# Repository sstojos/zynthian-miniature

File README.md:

# zynthian-miniature
# Overview
This is repository that store schematics and PCB design for basic PCB with MIDIs, Sound Card and 4 encoders for [zynthian](https://www.zynthian.org). It can also be used for any other raspberry pi audio software. 

This is designed in KiCad 6.0. It is inspired by clumsy MIDI project.

It comes as a single PCB that need to be split into 5: one main PCB and 4 encoder PCBs.

Here is the KiCad schematics screenshot:

# BOM
Interactive BOM can be found [here](https://raw.githack.com/sstojos/zynthian-miniature/main/bom/ibom.html).

# Usage scenarious

## JST connectors can be replaced with pinheader connectors
Connectors for encoder wiring are JST 2.5mm connectors but standard 2.54mm pin header connectors can also be used instead.

## PCB mounted MIDI connectors can be replaced with panel mounted MIDI connectors
It can be also used  with MIDI and AUDIO panel connectors. Here is how would you wire external panel connectors.

NOTE: Due to limited size of raspberry pi HUT, JST connectors for MIDI panel connectors are in the same place on PCB where two (IN and OUT) MIDI PCB mountable connectors are. Therefore you can only install JST connectors or MIDI PCB connectors but not both on the same PCB. MIDI through connector is only available through JST connector.

## It can be used with another sound card 
Sound card must not be installed if another sound card is connected to raspberry pi. I2S sound cards can not share the same rpi pins.

NOTE: can not be used with another audio card that have AUDIO IN (ADC) such as Hifyberry DAC+ ADC or DAC2 PRO ADC because encoder 3 B pin is wired to RPI pin 38 which is often  used by audio cards with ADC for audio in data. In this case there is a need to brake line from encoder 3 B connector to rpi 38 pin on PCB and  patch (solder wire) from encoder 3 b pin to another available rpi pin. Finnaly, wiring configuration in zynthian webconfig need to be changed accordingly. It is an easy patch. 

# Zynthian Webconfig

## Sound Card
Audio: HifiBerry DAC+ light

## Wiring
* Wiring Layout: Dummies
* Advance Configuration: Enabled
* Encoders A-pins: 5,3,28,23
* Encoders B-pins: 4,2,27,22
* Switches pins: 7,25,26,21

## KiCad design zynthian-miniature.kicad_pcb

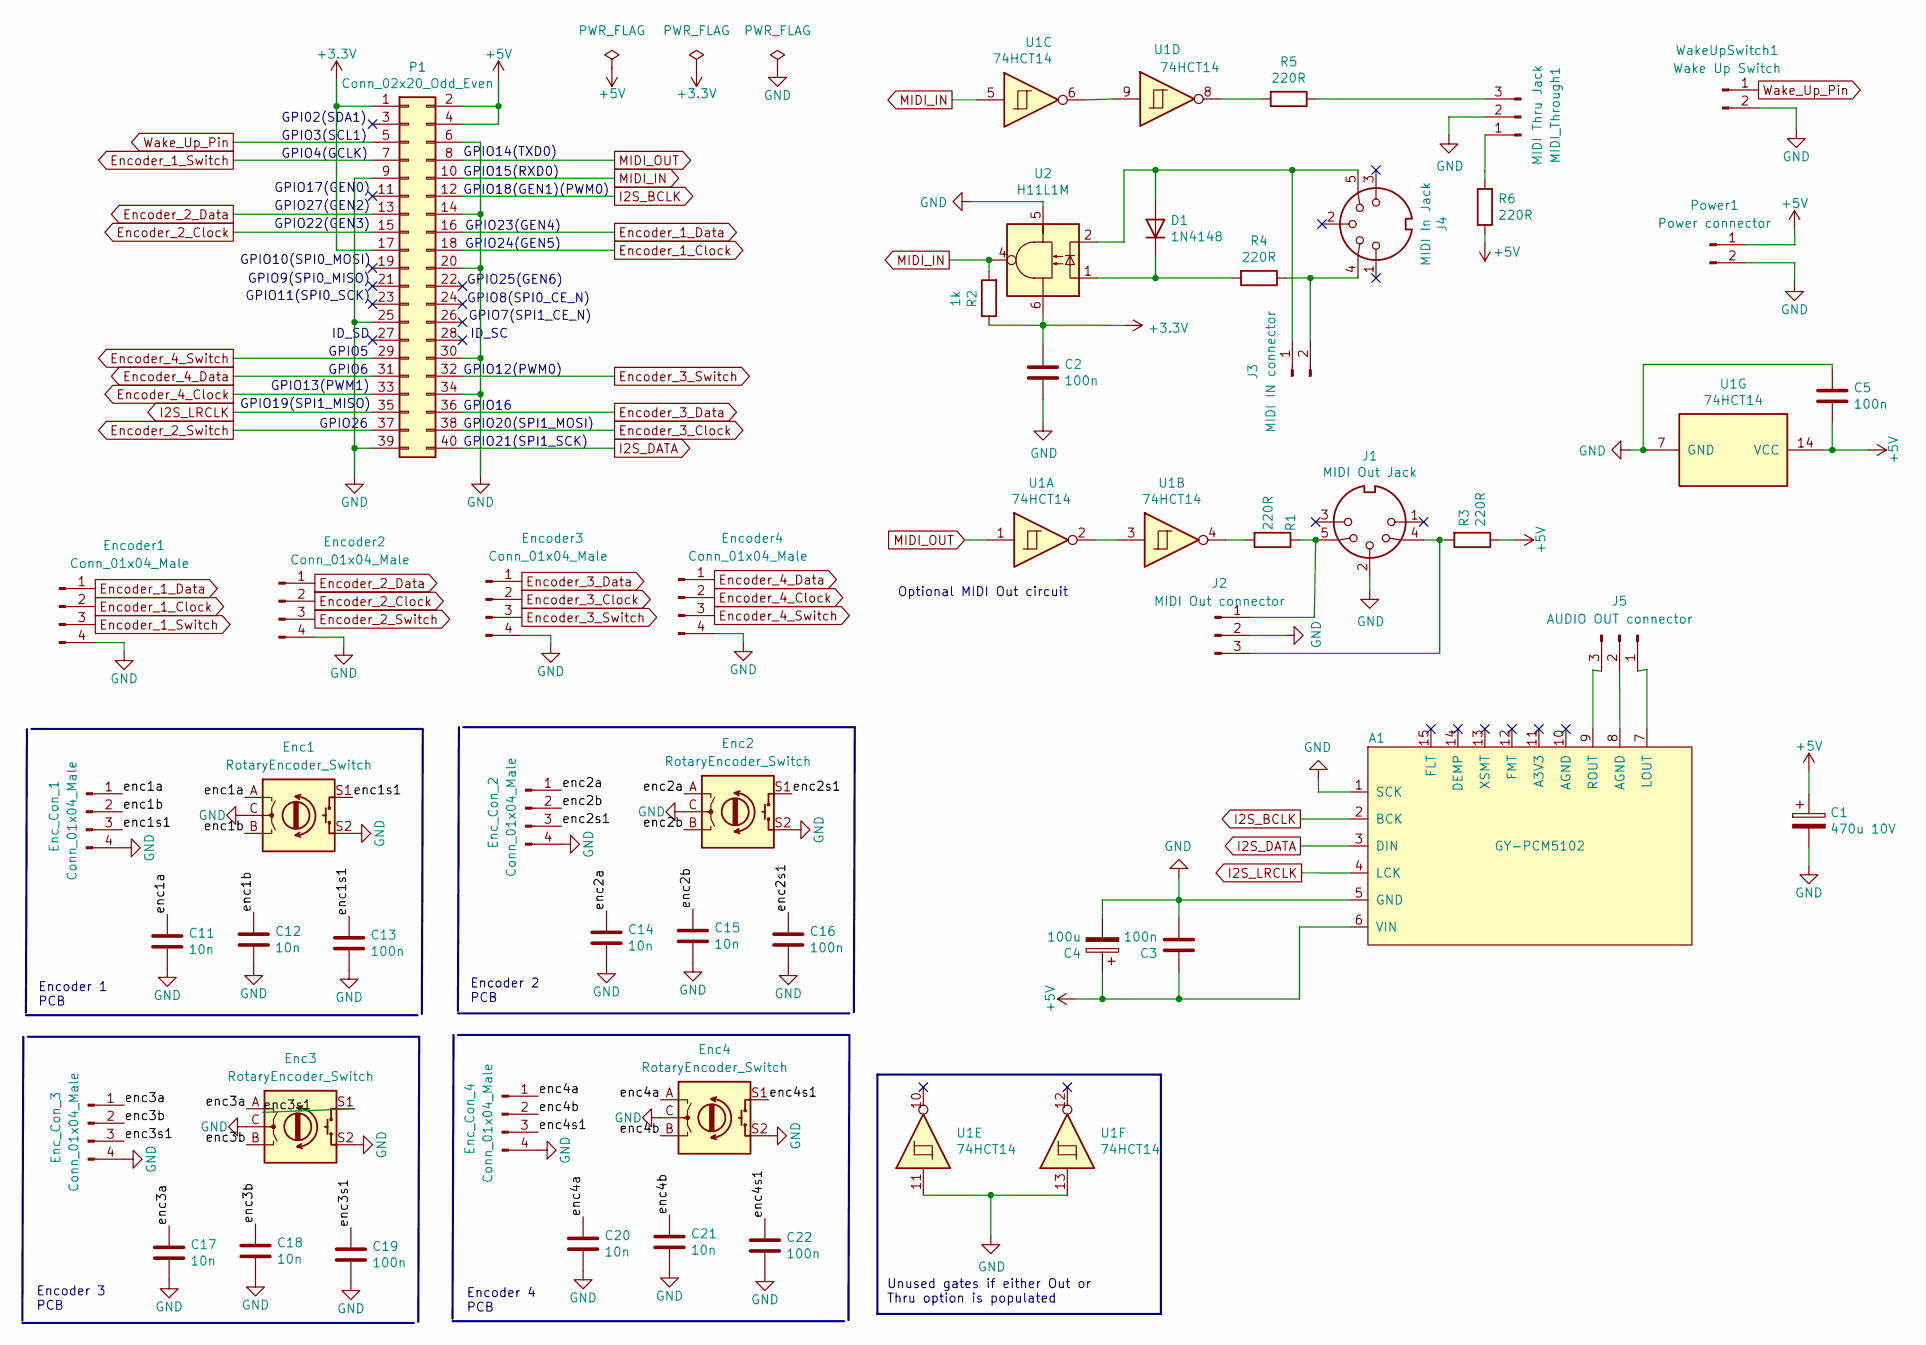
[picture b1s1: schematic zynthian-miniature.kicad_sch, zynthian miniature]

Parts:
A1: GY-PCM5102
C1: 470u 10V; CP_Radial_D8.0mm_P3.50mm
C2, C3, C5: 100n; C_Rect_L7.0mm_W2.0mm_P5.00mm
C4: 100u; CP_Radial_D6.3mm_P2.50mm
C11, C12, C14, C15, C17, C18, C20, C21: 10n; C_Rect_L4.0mm_W2.5mm_P2.50mm
C13, C16, C19, C22: 100n; C_Rect_L4.0mm_W2.5mm_P2.50mm
D1: 1N4148; D_DO-35_SOD27_P7.62mm_Horizontal
Enc1, Enc2, Enc3, Enc4: RotaryEncoder_Switch; RotaryEncoder_Alps_EC12E-Switch_Vertical_H20mm
Enc_Con_1, Enc_Con_2, Enc_Con_3, Enc_Con_4: Conn_01x04_Male; PinHeader_1x04_P2.54mm_Vertical
Encoder1, Encoder2, Encoder3, Encoder4: Conn_01x04_Male; PinHeader_1x04_P2.54mm_Vertical
J1: MIDI Out Jack; MultiDIN5
J2: MIDI Out connector; PinHeader_1x03_P2.54mm_Vertical
J3: MIDI IN connector; PinHeader_1x02_P2.54mm_Vertical
J4: MIDI In Jack; MultiDIN5
J5: AUDIO OUT connector; PinHeader_1x03_P2.54mm_Vertical
MIDI_Through1: MIDI Thru Jack; PinHeader_1x03_P2.54mm_Vertical
P1: Conn_02x20_Odd_Even; PinSocket_2x20_P2.54mm_Vertical
Power1: Power connector; PinHeader_1x02_P2.54mm_Vertical
R1, R3, R4, R5, R6: 220R; R_Axial_DIN0207_L6.3mm_D2.5mm_P7.62mm_Horizontal
R2: 1k; R_Axial_DIN0207_L6.3mm_D2.5mm_P7.62mm_Horizontal
U1: 74HCT14; DIP-14_W7.62mm
U2: H11L1M; DIP-6_W7.62mm
WakeUpSwitch1: Wake Up Switch; PinHeader_1x02_P2.54mm_Vertical

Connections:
+3.3V: C2.1, P1.1, P1.17, R2.1, U2.6
+5V: A1.6 (VIN), C1.1, C3.1, C4.1, C5.2, P1.2, P1.4, Power1.1, R3.1, R6.1, U1.14 (VCC)
/enc1a: C11.1, Enc1.A, Enc_Con_1.1
/enc1b: C12.1, Enc1.B, Enc_Con_1.2
/enc1s1: C13.1, Enc1.S1, Enc_Con_1.3
/enc2a: C14.1, Enc2.A, Enc_Con_2.1
/enc2b: C15.1, Enc2.B, Enc_Con_2.2
/enc2s1: C16.1, Enc2.S1, Enc_Con_2.3
/enc3a: C17.1, Enc3.A, Enc_Con_3.1
/enc3b: C18.1, Enc3.B, Enc_Con_3.2
/enc3s1: C19.1, Enc3.S1, Enc_Con_3.3
/enc4a: C20.1, Enc4.A, Enc_Con_4.1
/enc4b: C21.1, Enc4.B, Enc_Con_4.2
/enc4s1: C22.1, Enc4.S1, Enc_Con_4.3
Encoder_1_Clock: Encoder1.2, P1.18
Encoder_1_Data: Encoder1.1, P1.16
Encoder_1_Switch: Encoder1.3, P1.7
Encoder_2_Clock: Encoder2.2, P1.15
Encoder_2_Data: Encoder2.1, P1.13
Encoder_2_Switch: Encoder2.3, P1.37
Encoder_3_Clock: Encoder3.2, P1.38
Encoder_3_Data: Encoder3.1, P1.36
Encoder_3_Switch: Encoder3.3, P1.32
Encoder_4_Clock: Encoder4.2, P1.33
Encoder_4_Data: Encoder4.1, P1.31
Encoder_4_Switch: Encoder4.3, P1.29
GND: A1.1 (SCK), A1.5 (GND), C1.2, C2.2, C3.2, C4.2, C5.1, C11.2, C12.2, C13.2, C14.2, C15.2, C16.2, C17.2, C18.2, C19.2, C20.2, C21.2, C22.2, Enc1.C, Enc1.S2, Enc2.C, Enc2.S2, Enc3.C, Enc3.S2, Enc4.C, Enc4.S2, Enc_Con_1.4, Enc_Con_2.4, Enc_Con_3.4, Enc_Con_4.4, Encoder1.4, Encoder2.4, Encoder3.4, Encoder4.4, J1.2, J2.2, MIDI_Through1.2, P1.6, P1.9, P1.14, P1.20, P1.25, P1.30, P1.34, P1.39, Power1.2, U1.7 (GND), U1.11, U1.13, U2.5, WakeUpSwitch1.2
I2S_BCLK: A1.2 (BCK), P1.12
I2S_DATA: A1.3 (DIN), P1.40
I2S_LRCLK: A1.4 (LCK), P1.35
MIDI_IN: P1.10, R2.2, U1.5, U2.4
MIDI_OUT: P1.8, U1.1
unnamed: A1.7 (LOUT), J5.1
unnamed: A1.8 (AGND), J5.2
unnamed: A1.9 (ROUT), J5.3
unnamed: D1.1 (K), R4.2, U2.1
unnamed: D1.2 (A), J3.1, J4.5, U2.2
unnamed: J1.4, J2.3, R3.2
unnamed: J1.5, J2.1, R1.1
unnamed: J3.2, J4.4, R4.1
unnamed: MIDI_Through1.1, R6.2
unnamed: MIDI_Through1.3, R5.1
unnamed: R1.2, U1.4
unnamed: R5.2, U1.8
unnamed: U1.2, U1.3
unnamed: U1.6, U1.9
Wake_Up_Pin: P1.5, WakeUpSwitch1.1

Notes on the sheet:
Encoder 1 PCB
GPIO13(PWM1)
ID_SC
GPIO22(GEN3)
GPIO7(SPI1_CE_N)
Encoder 3 PCB
GPIO12(PWM0)
Encoder 2 PCB
GPIO25(GEN6)
ID_SD
GPIO23(GEN4)
GPIO6
GPIO15(RXD0)
GPIO26
Encoder 4 PCB
GPIO10(SPI0_MOSI)
GPIO9(SPI0_MISO)
GPIO27(GEN2)
GPIO14(TXD0)
GPIO24(GEN5)
GPIO11(SPI0_SCK)
Optional MIDI Out circuit
GPIO5
GPIO19(SPI1_MISO)
Unused gates if either Out or Thru option is populated
GPIO17(GEN0)
GPIO4(GCLK)
GPIO8(SPI0_CE_N)
GPIO20(SPI1_MOSI)
GPI02(SDA1)
GPIO18(GEN1)(PWM0)
GPIO21(SPI1_SCK)
GPIO3(SCL1)
GPIO16

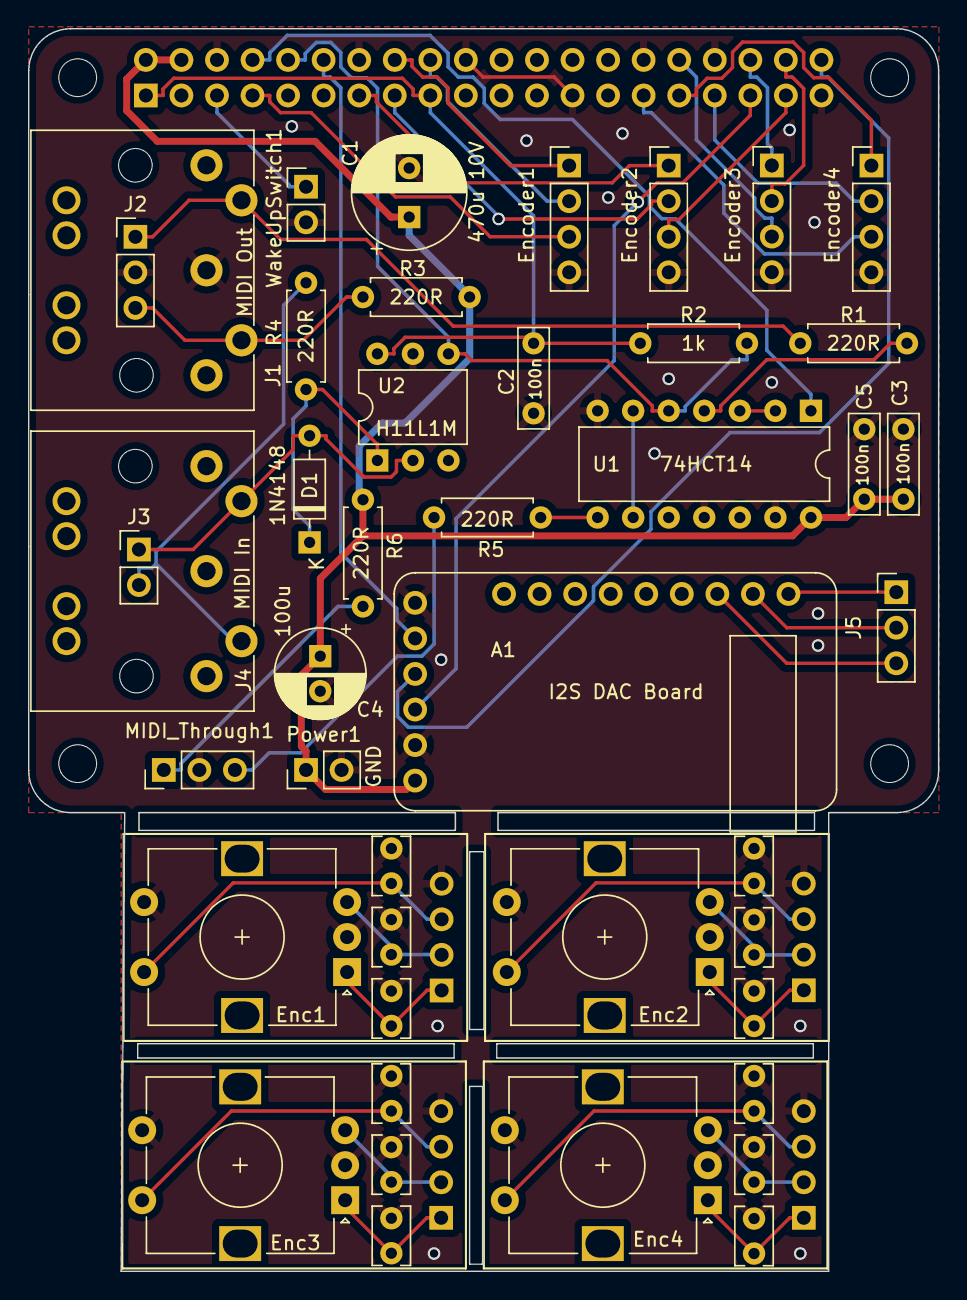
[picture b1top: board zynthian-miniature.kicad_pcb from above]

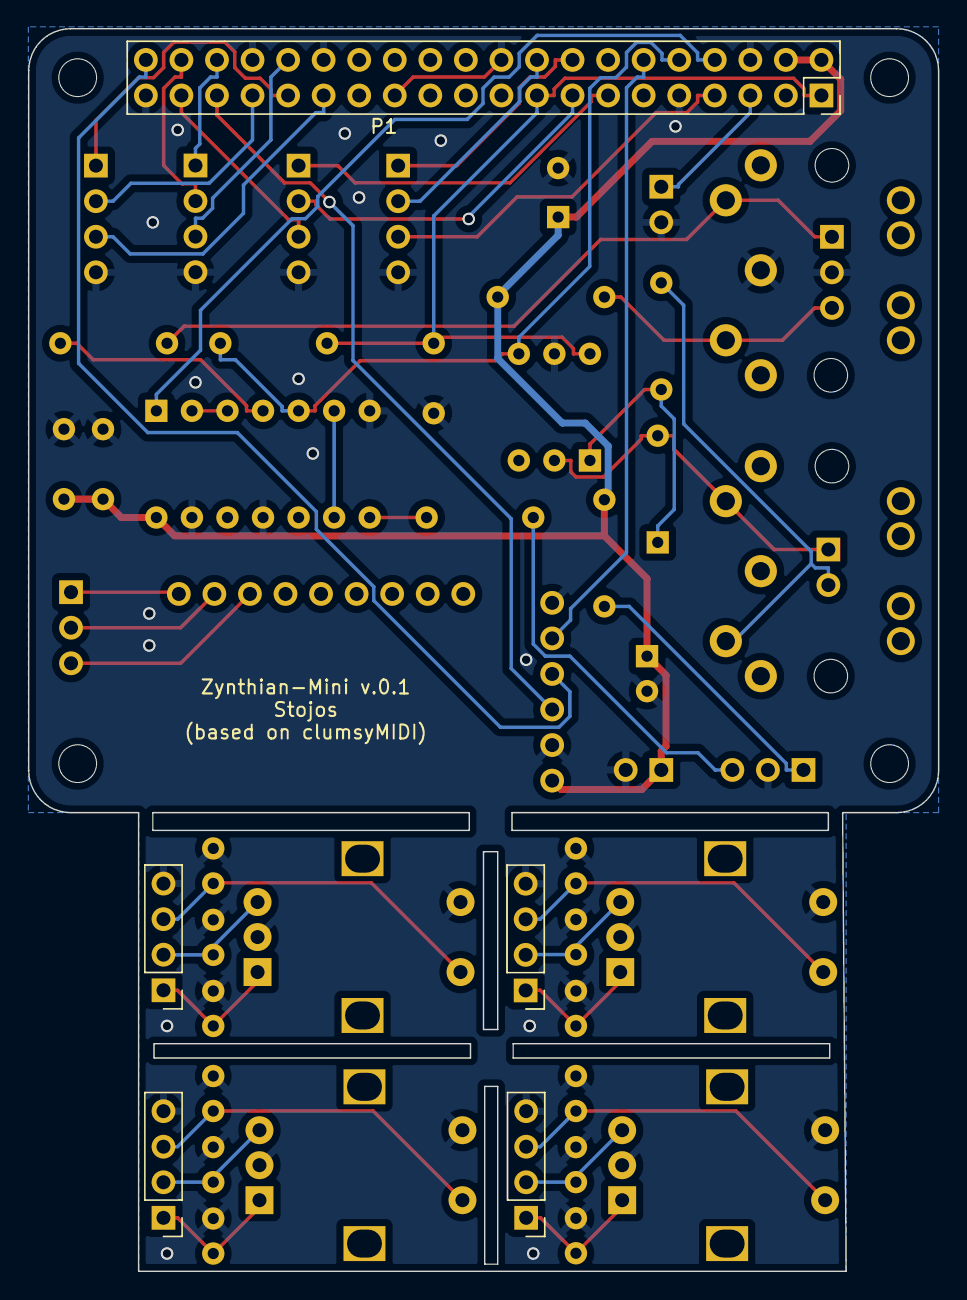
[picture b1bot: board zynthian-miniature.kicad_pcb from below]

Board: 2 copper layers, 65.0 x 88.8 mm, 52 parts (5 on the bottom side), 47 nets.

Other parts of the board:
MK1, MK2, MK3, MK4: M2.5; MountingHole_2.7mm_M2.5

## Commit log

2024-06-11 first release
2024-06-11 added schematics
